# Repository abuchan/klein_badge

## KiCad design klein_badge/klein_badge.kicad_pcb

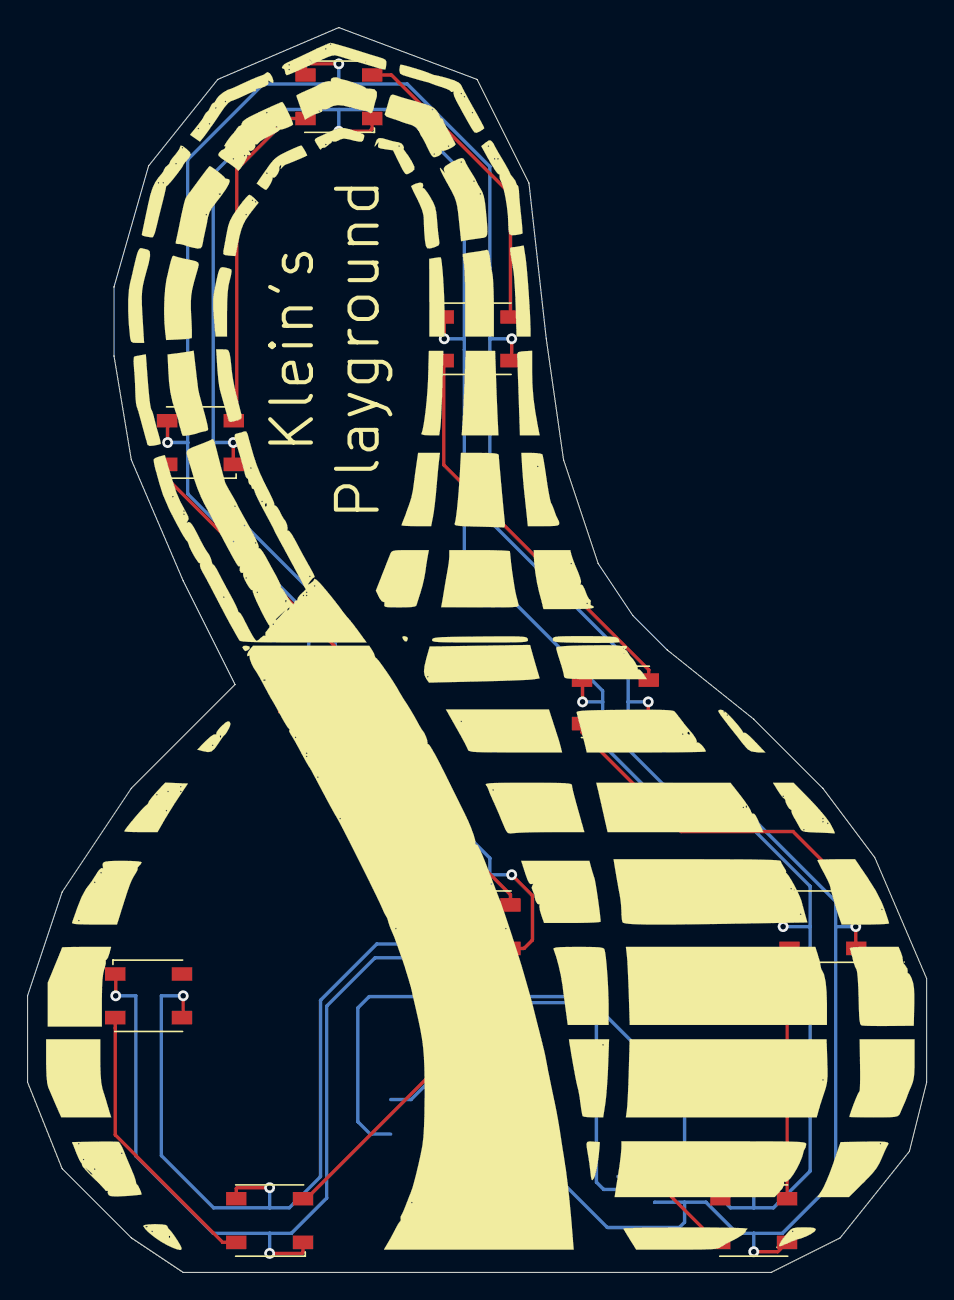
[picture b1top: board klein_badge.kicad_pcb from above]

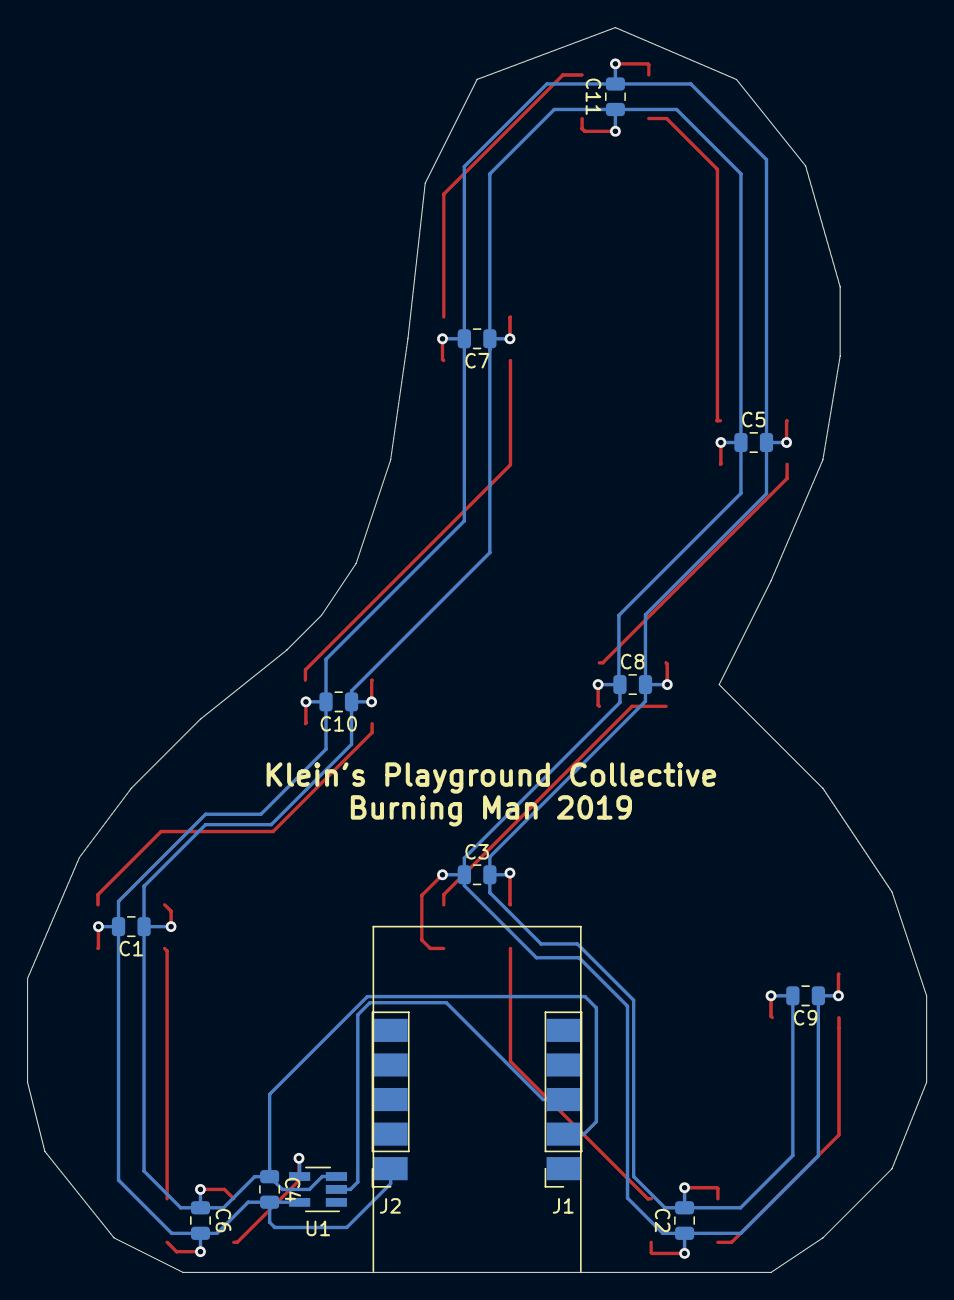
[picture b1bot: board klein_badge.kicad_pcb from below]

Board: 2 copper layers, 66.0 x 91.4 mm, 24 parts (14 on the bottom side), 13 nets.

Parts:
C1, C2, C3, C4, C5, C6, C7, C8, C9, C10, C11: C; C_0805_2012Metric
D1, D2, D3, D4, D5, D6, D7, D8, D9, D10: Inolux_IN-PI554FCH; LED_Inolux_IN-PI554FCH_PLCC4_5.0x5.0mm_P3.2mm
J1, J2: Conn_01x05; header_1x05_SMD
U1: 74AUC1G07; SOT-23-5_HandSoldering

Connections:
+5V: C1.2, C2.2, C3.2, C4.2, C5.2, C6.2, C7.2, C8.2, C9.2, C10.2, C11.2, D1.3, D2.3, D3.3, D4.3, D5.3, D6.3, D7.3, D8.3, D9.3, D10.3, J2.1, U1.5
GND: C1.1, C2.1, C3.1, C4.1, C5.1, C6.1, C7.1, C8.1, C9.1, C10.1, C11.1, D1.1, D2.1, D3.1, D4.1, D5.1, D6.1, D7.1, D8.1, D9.1, D10.1, J1.2, U1.3
unnamed: D1.2, U1.4
unnamed: D1.4, D2.2
unnamed: D2.4, D3.2
unnamed: D3.4, D4.2
unnamed: D4.4, D5.2
unnamed: D5.4, D6.2
unnamed: D6.4, D7.2
unnamed: D7.4, D8.2
unnamed: D8.4, D9.2
unnamed: D9.4, D10.2
unnamed: J1.3, U1.2

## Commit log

2019-08-13 Schematic pretty much done.
2019-08-13 Assigned footprints and imported to PCB.
2019-08-13 Added images to get silkscreen, did rough layout.
2019-08-13 Finished routing.
2019-08-13 Exported Gerbers.
2019-08-21 Adding main.py for Trinket upload.
2019-08-21 Added stripes to patterns
